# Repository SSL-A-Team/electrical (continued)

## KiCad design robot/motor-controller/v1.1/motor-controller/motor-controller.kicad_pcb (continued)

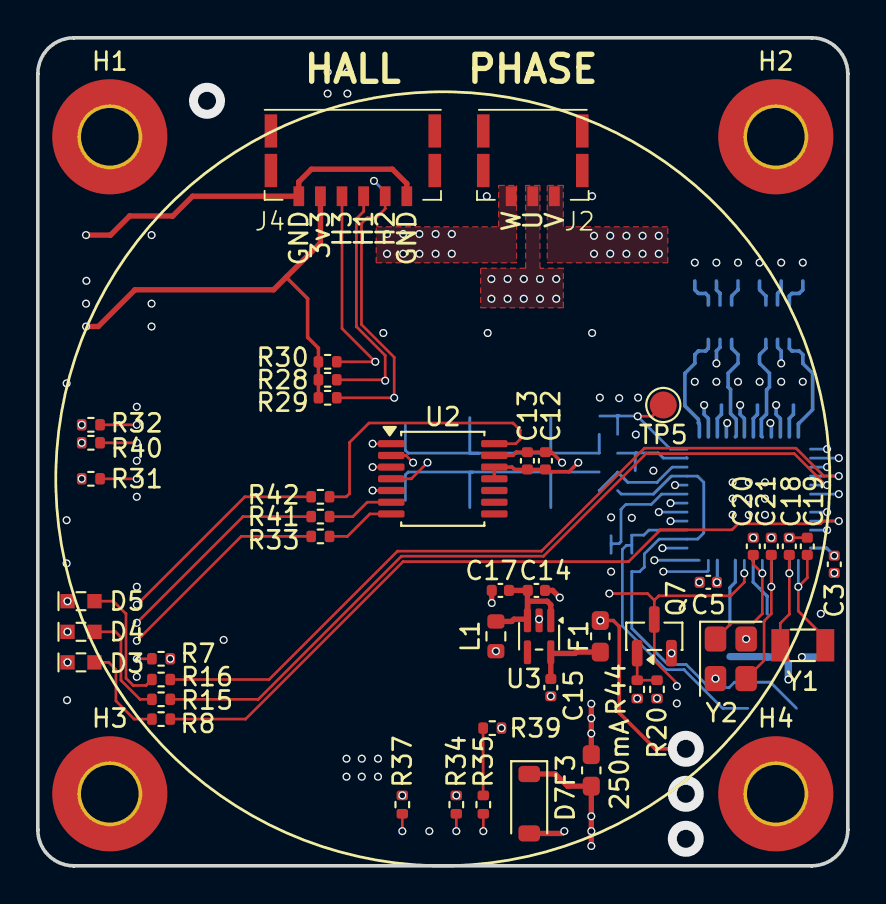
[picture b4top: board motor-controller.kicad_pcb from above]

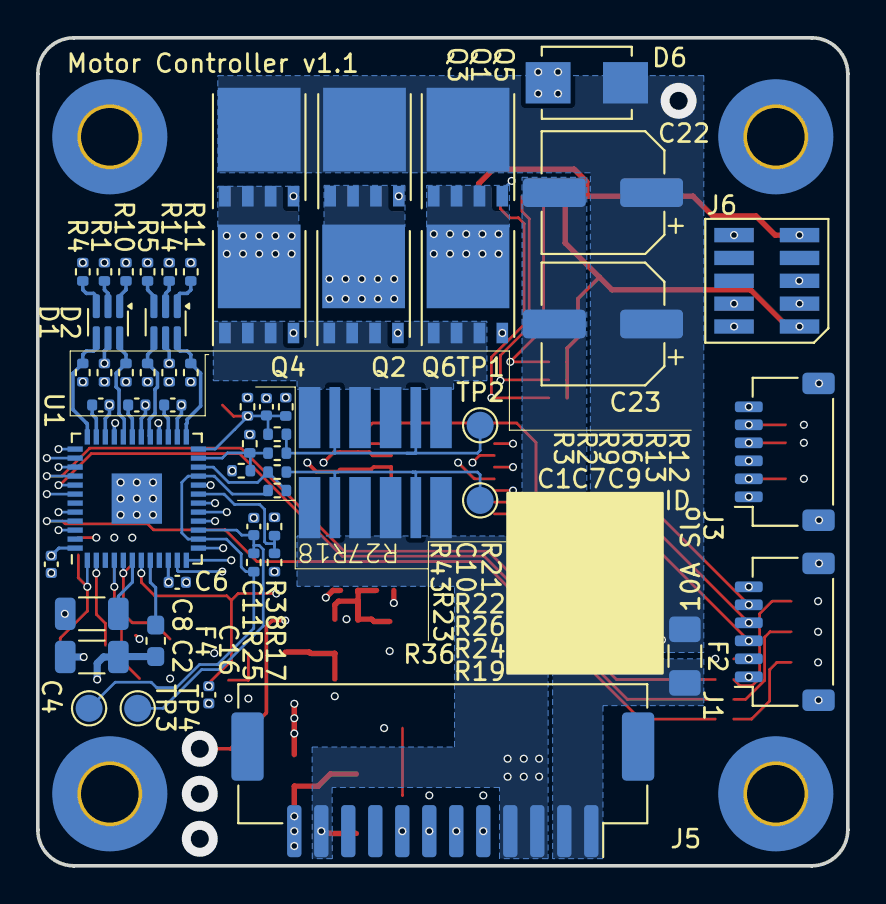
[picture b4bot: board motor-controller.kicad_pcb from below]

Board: 6 copper layers, 45.0 x 46.0 mm, 106 parts (57 on the bottom side), 76 nets.

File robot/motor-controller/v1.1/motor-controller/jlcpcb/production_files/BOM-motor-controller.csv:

Comment,Designator,Footprint,LCSC,Quantity
0,"R33,R39,R41,R42",R_0402_1005Metric,C17168,4
0.1uF 63V,"C1,C13,C14,C16,C4,C6,C7,C9",C_0402_1005Metric,C131394,8
0467.250NRHF,F3,Fuse_0603_1608Metric_Pad1.05x0.95mm_HandSolder,C151137,1
0501010.WR1,F2,Fuse_1206_3216Metric_Pad1.42x1.75mm_HandSolder,C207003,1
06F-0200L1,"F1,F4",Fuse_0603_1608Metric_Pad1.05x0.95mm_HandSolder,C377220,2
10,"R1,R10,R11,R14,R4,R5",R_0402_1005Metric,C25077,6
100k,"R20,R34,R37",R_0402_1005Metric,C25741,3
10k,"R15,R16,R28,R29,R30,R31,R32,R40,R44,R7,R8",R_0402_1005Metric,C60490,11
11.5k,R17,R_0402_1005Metric,C270653,1
11pF,"C20,C21",C_0402_1005Metric,C161525,2
13.7k 1%,R19,R_0402_1005Metric,C852522,1
15.0k 1%,R36,R_0402_1005Metric,C853539,1
15pF,"C18,C19",C_0402_1005Metric,C86285,2
165k 1%,R23,R_0402_1005Metric,C1509613,1
1k,R38,R_0402_1005Metric,C11702,1
1k 1%,,R_0402_1005Metric,C11702,0
1uF 10V,"C11,C12,C15,C17,C3,C5",C_0402_1005Metric,C14445,6
1uF 63V,"C2,C8",C_1206_3216Metric,C70463,2
2.49k 1%,"R22,R24,R26",R_0402_1005Metric,C852700,3
22uF 6.3V,C10,C_0402_1005Metric,C415703,1
30k 1%,,R_0402_1005Metric,C25776,0
330,R35,R_0402_1005Metric,C25104,1
62,"R12,R13,R2,R3,R6,R9",R_0402_1005Metric,C100501,6
62 1%,R25,R_0402_1005Metric,C852875,1
650 @100MHz,L1,R_0603_1608Metric,C21189,1
AS5047P,U2,TSSOP-14_4.4x5mm_P0.65mm,C962063,1
BAS16VY,"D1,D2",SOT-363_SC-70-6,C135826,2
BM03B-ACHFKS,J2,JST_ACHFR_03V,C5177195,1
BM06B-ACHFKS,J4,JST_ACHFR_06V,C5304907,1
BSS138K,Q7,SOT-23,C5224263,1
Conn_ARM_JTAG_SWD_10,J6,Samtec-2x5pin-1.27mm,C448647,1
EEEFT1V101AP,"C22,C23",CP_Elec_6.3x5.8,C128464,2
HoLLR2512-3W-100mR-1%,"R18,R27",2512_CS_ADI-TypeC,C2994646,2
Q13FC13500005,Y1,Crystal_SMD_3215-2Pin_3.2x1.5mm,C841881,1
SM06B-SRSS-TB,J3,JST_SH_SM06B-SRSS-TB_1x06-1MP_P1.00mm_Horizontal,C160405,1
SMBJ26CA,D6,D_SMB_Non-Polar,C135063,1
SMF3.3CA,D7,D_SOD-123,C6165153,1
STL90N10F7,"Q1,Q2,Q3,Q4,Q5,Q6",PowerFLAT_5x6,C457493,6
STSPIN32F0B,U1,QFN-48-1EP_7x7mm_P0.5mm_EP2.8x2.8mm,C1521053,1
TAXM8M4RDBCCT2T,Y2,Crystal_SMD_3225-4Pin_3.2x2.5mm,C400090,1
TLV70030_SOT353,U3,SOT-353_SC-70-5,C527437,1
XL-1608SURC-06,D5,LED0603,C965799,1
XL-1608UGC-04,D4,LED0603,C965804,1
XL-1608UOC-06,D3,LED0603,C965800,1
SM12B-ZESS,J5,JST_ZE_SM12B-ZESS-TB_1x12-1MP_P1.50mm_Horizontal,,1

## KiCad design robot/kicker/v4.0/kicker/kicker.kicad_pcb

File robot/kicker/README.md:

# Kicker Boards

Subfolders contain various versions of the kicker board. A summary is included below.

## Kicker Version Summary

 - v1.1.0_fe - Nonviable, check errata
 - v1.1.0_ufd - Nonviable, check errata
 - v1.0.0 - Nonviable, check errata
 - v2.0.0 - Patchable, check errata
 - v3.0 - Patchable, check errata
 - v3.1 - Functional, minor patching suggested

## KiCad Version Summary

 - v3.1 - KiCad v7.X
 - v3.0 - KiCad v7.X
 - v2.0.0 - KiCad v7.X
 - v1.1.0 - KiCad v7.X
 - v1.0.0 - KiCad v6.99 (nightly)

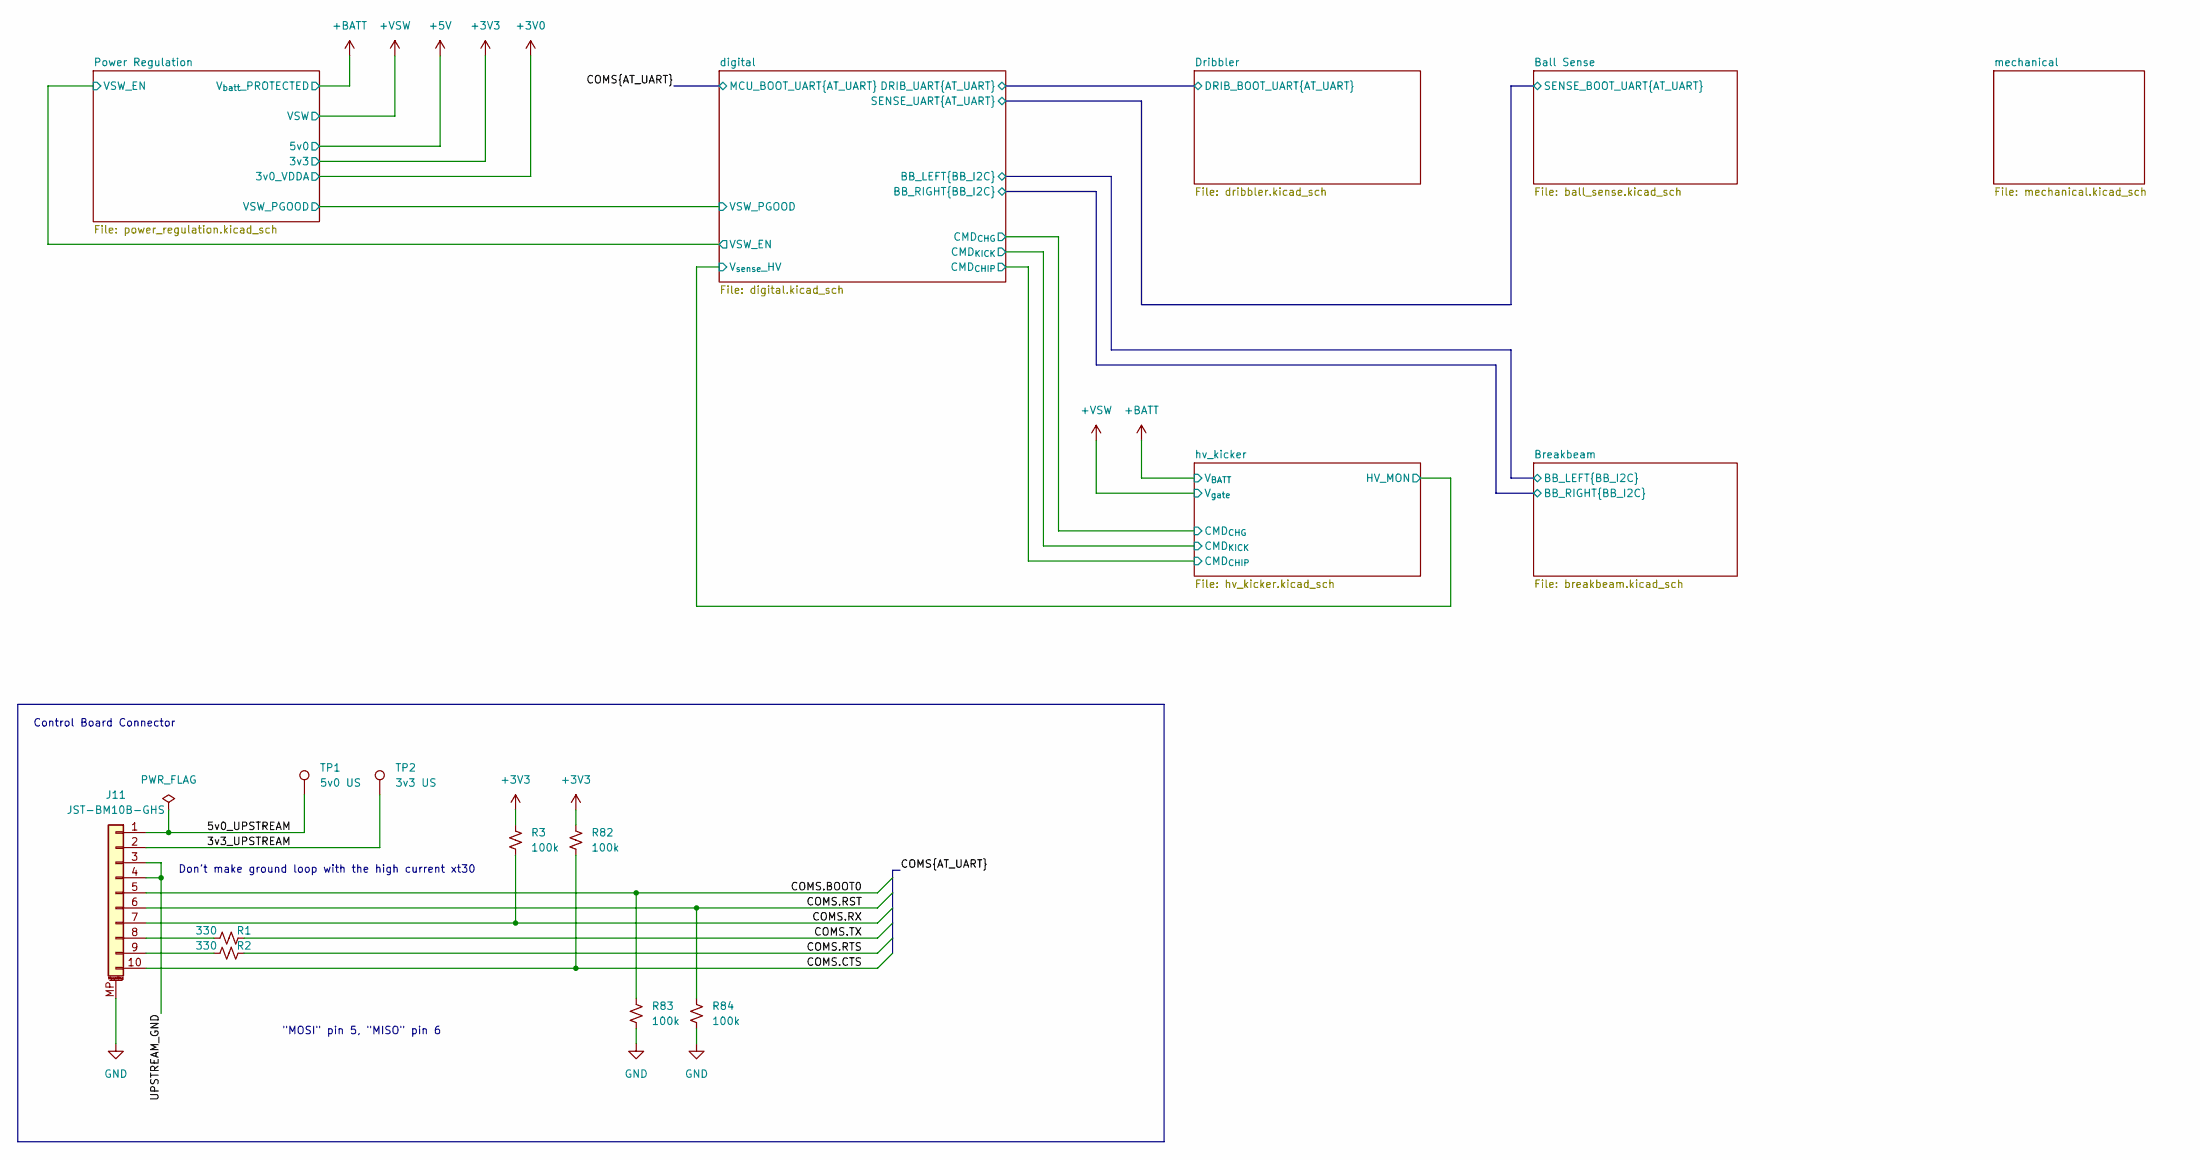
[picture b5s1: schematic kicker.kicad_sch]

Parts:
J11: JST-BM10B-GHS; JST_GH_BM10B-GHS-TBT_1x10-1MP_P1.25mm_Vertical; LCSC C2683602
R1, R2: 330; R_0402_1005Metric; LCSC C105875
R3, R82, R83, R84: 100k; R_0402_1005Metric; LCSC C60491
TP1: 5v0 US; TestPoint_Pad_D1.0mm
TP2: 3v3 US; TestPoint_Pad_D1.0mm

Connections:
+3V3: R3.1, R82.1; also elsewhere on the board
/3v3_UPSTREAM: J11.2, TP2.1
/5v0_UPSTREAM: J11.1, TP1.1
/COMS.BOOT0: J11.5, R83.1; also elsewhere on the board
/COMS.CTS: J11.10, R82.2; also elsewhere on the board
/COMS.RST: J11.6, R84.1; also elsewhere on the board
/COMS.RTS: R2.2; also elsewhere on the board
/COMS.RX: J11.7, R3.2; also elsewhere on the board
/COMS.TX: R1.2; also elsewhere on the board
/UPSTREAM_GND: J11.3, J11.4
GND: J11.MP (MountPin), R83.2, R84.2; also elsewhere on the board
unnamed: J11.8, R1.1
unnamed: J11.9, R2.1

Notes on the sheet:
Don't make ground loop with the high current xt30
Control Board Connector
"MOSI" pin 5, "MISO" pin 6

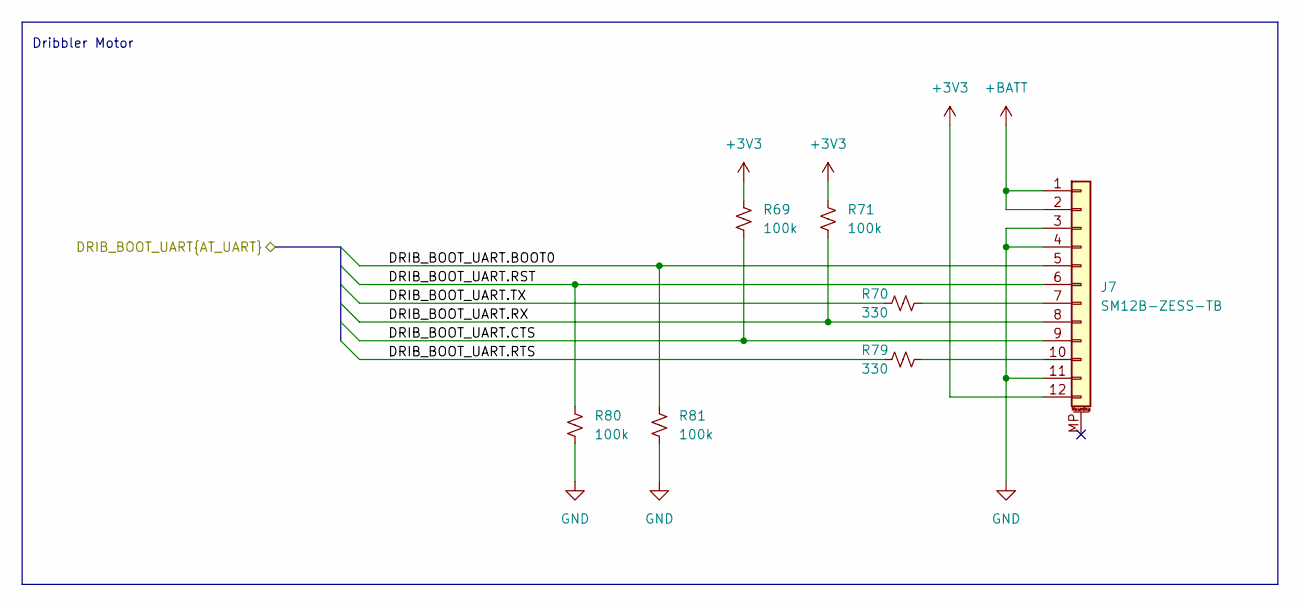
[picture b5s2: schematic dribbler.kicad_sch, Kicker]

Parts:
J7: SM12B-ZESS-TB; JST_ZE_BM12B-ZESS-TBT_1x12-1MP_P1.50mm_Vertical
R69, R71, R80, R81: 100k; R_0402_1005Metric; LCSC C60491
R70, R79: 330; R_0402_1005Metric; LCSC C105875

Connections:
+3V3: J7.12, R69.1, R71.1; also elsewhere on the board
+BATT: J7.1, J7.2; also elsewhere on the board
/Dribbler/DRIB_BOOT_UART.BOOT0: J7.5, R81.1; also elsewhere on the board
/Dribbler/DRIB_BOOT_UART.CTS: J7.9, R69.2; also elsewhere on the board
/Dribbler/DRIB_BOOT_UART.RST: J7.6, R80.1; also elsewhere on the board
/Dribbler/DRIB_BOOT_UART.RTS: R79.1; also elsewhere on the board
/Dribbler/DRIB_BOOT_UART.RX: J7.8, R71.2; also elsewhere on the board
/Dribbler/DRIB_BOOT_UART.TX: R70.1; also elsewhere on the board
GND: J7.3, J7.4, J7.11, R80.2, R81.2; also elsewhere on the board
unnamed: J7.7, R70.2
unnamed: J7.10, R79.2

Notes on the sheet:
Dribbler Motor

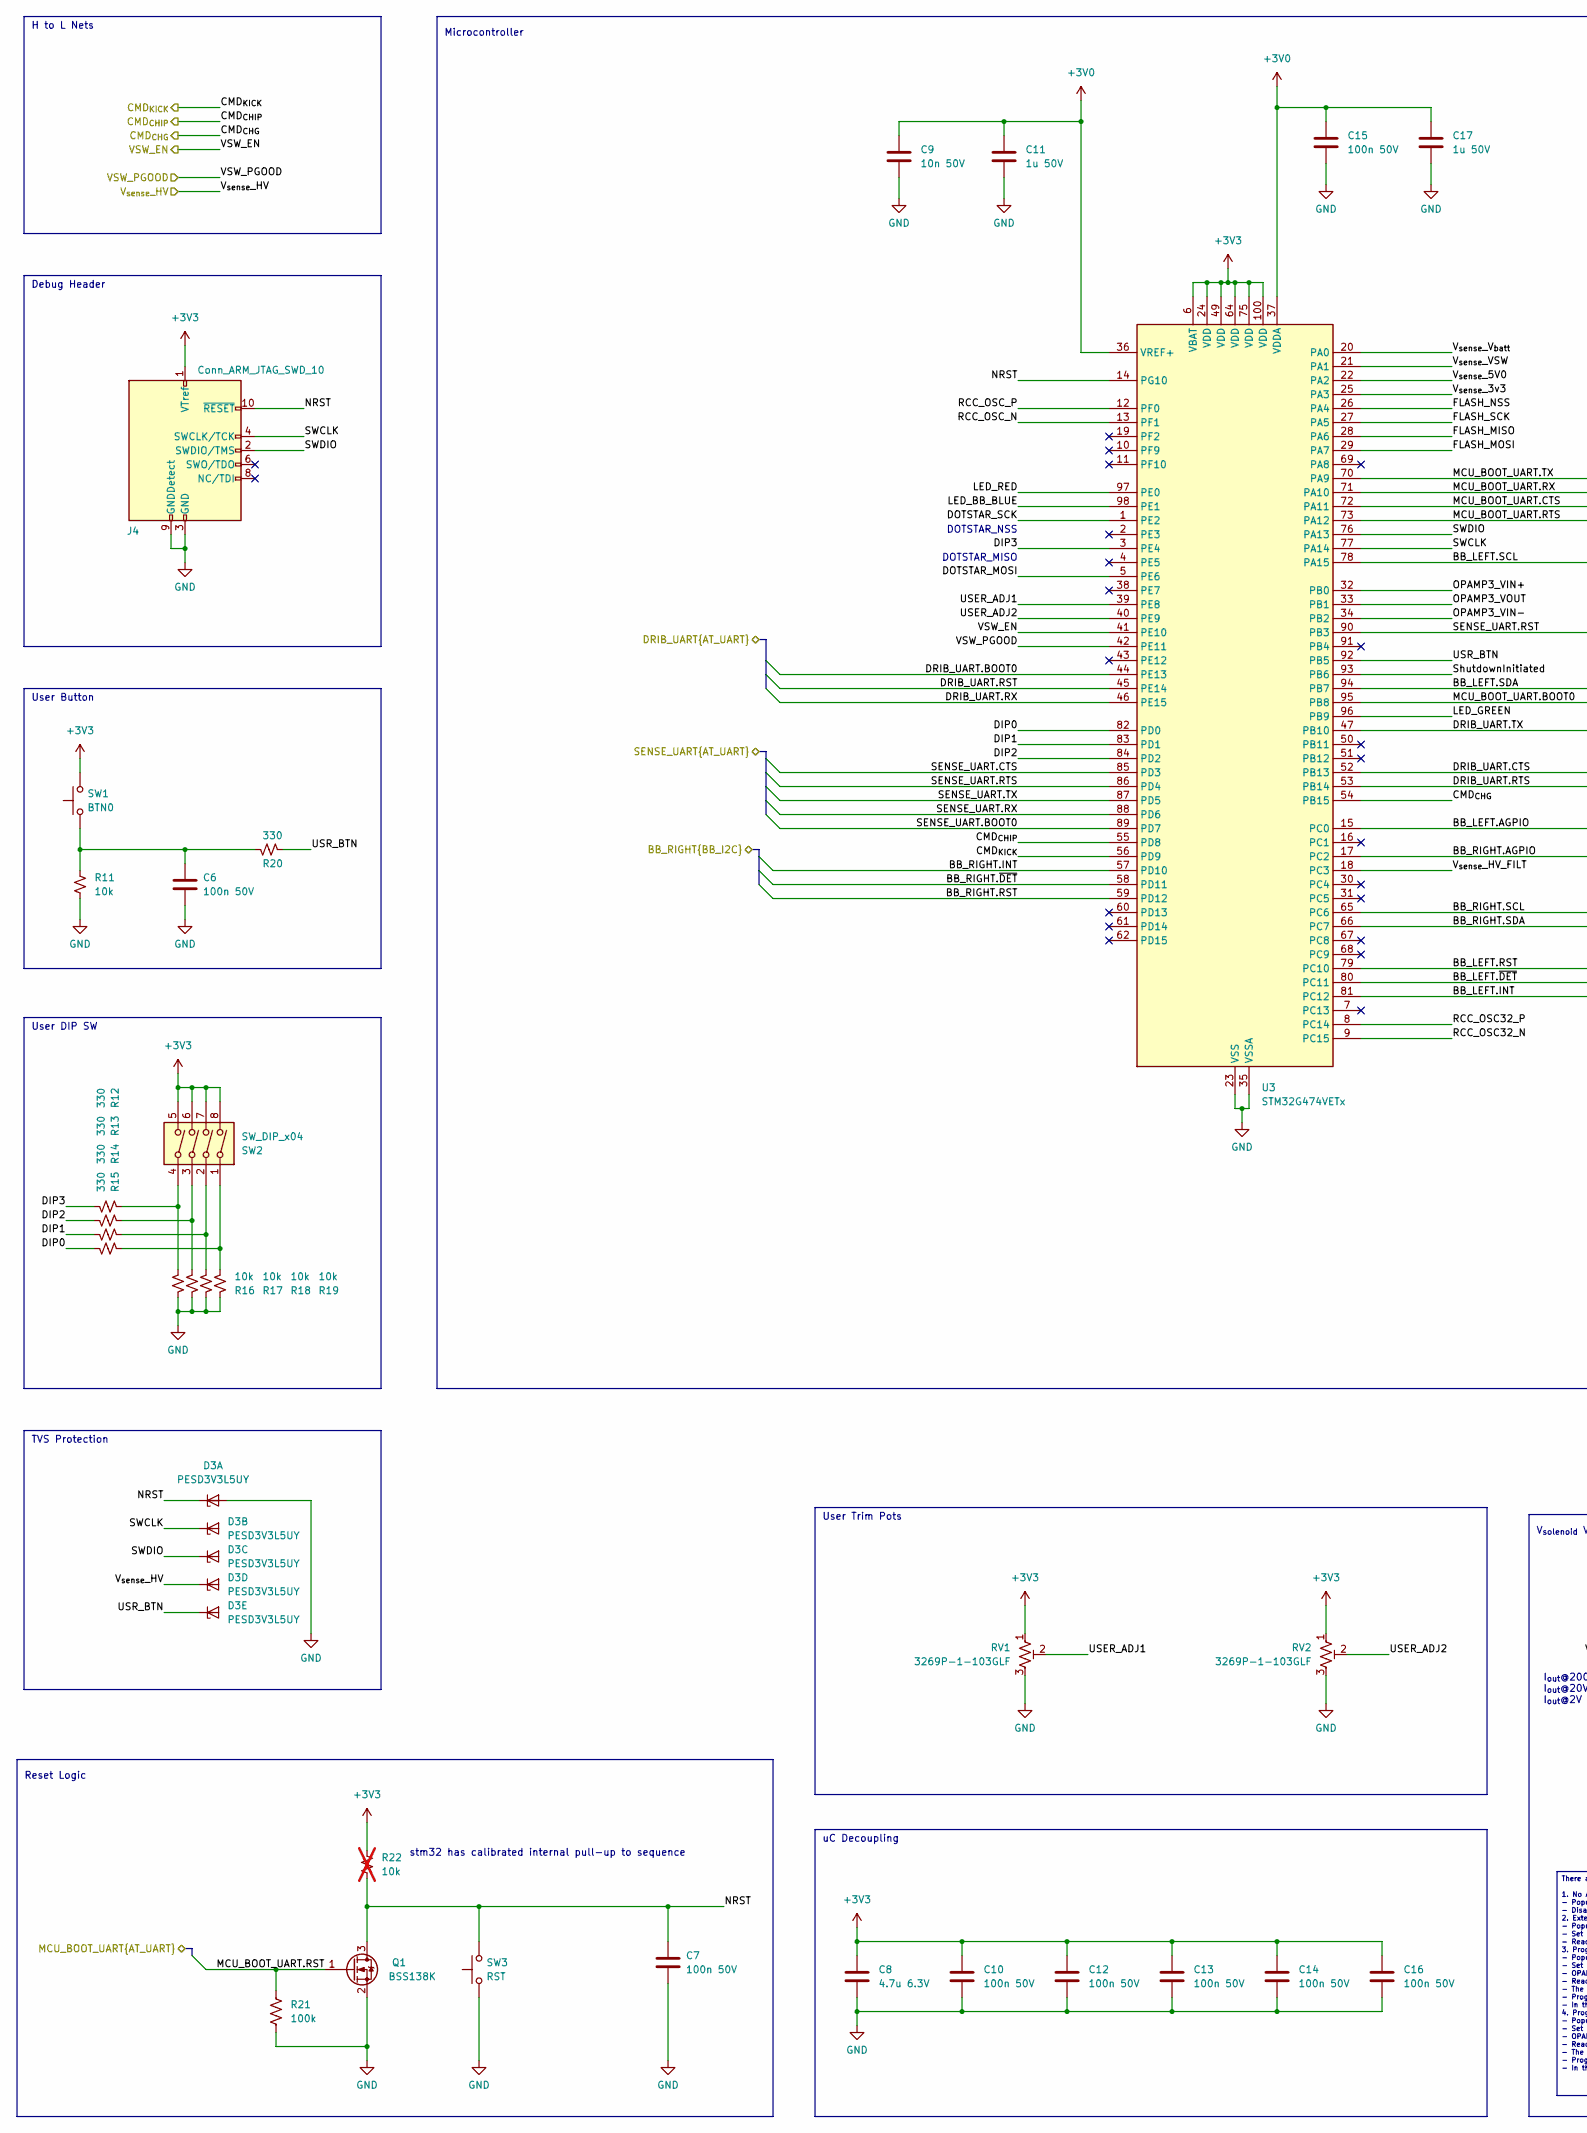
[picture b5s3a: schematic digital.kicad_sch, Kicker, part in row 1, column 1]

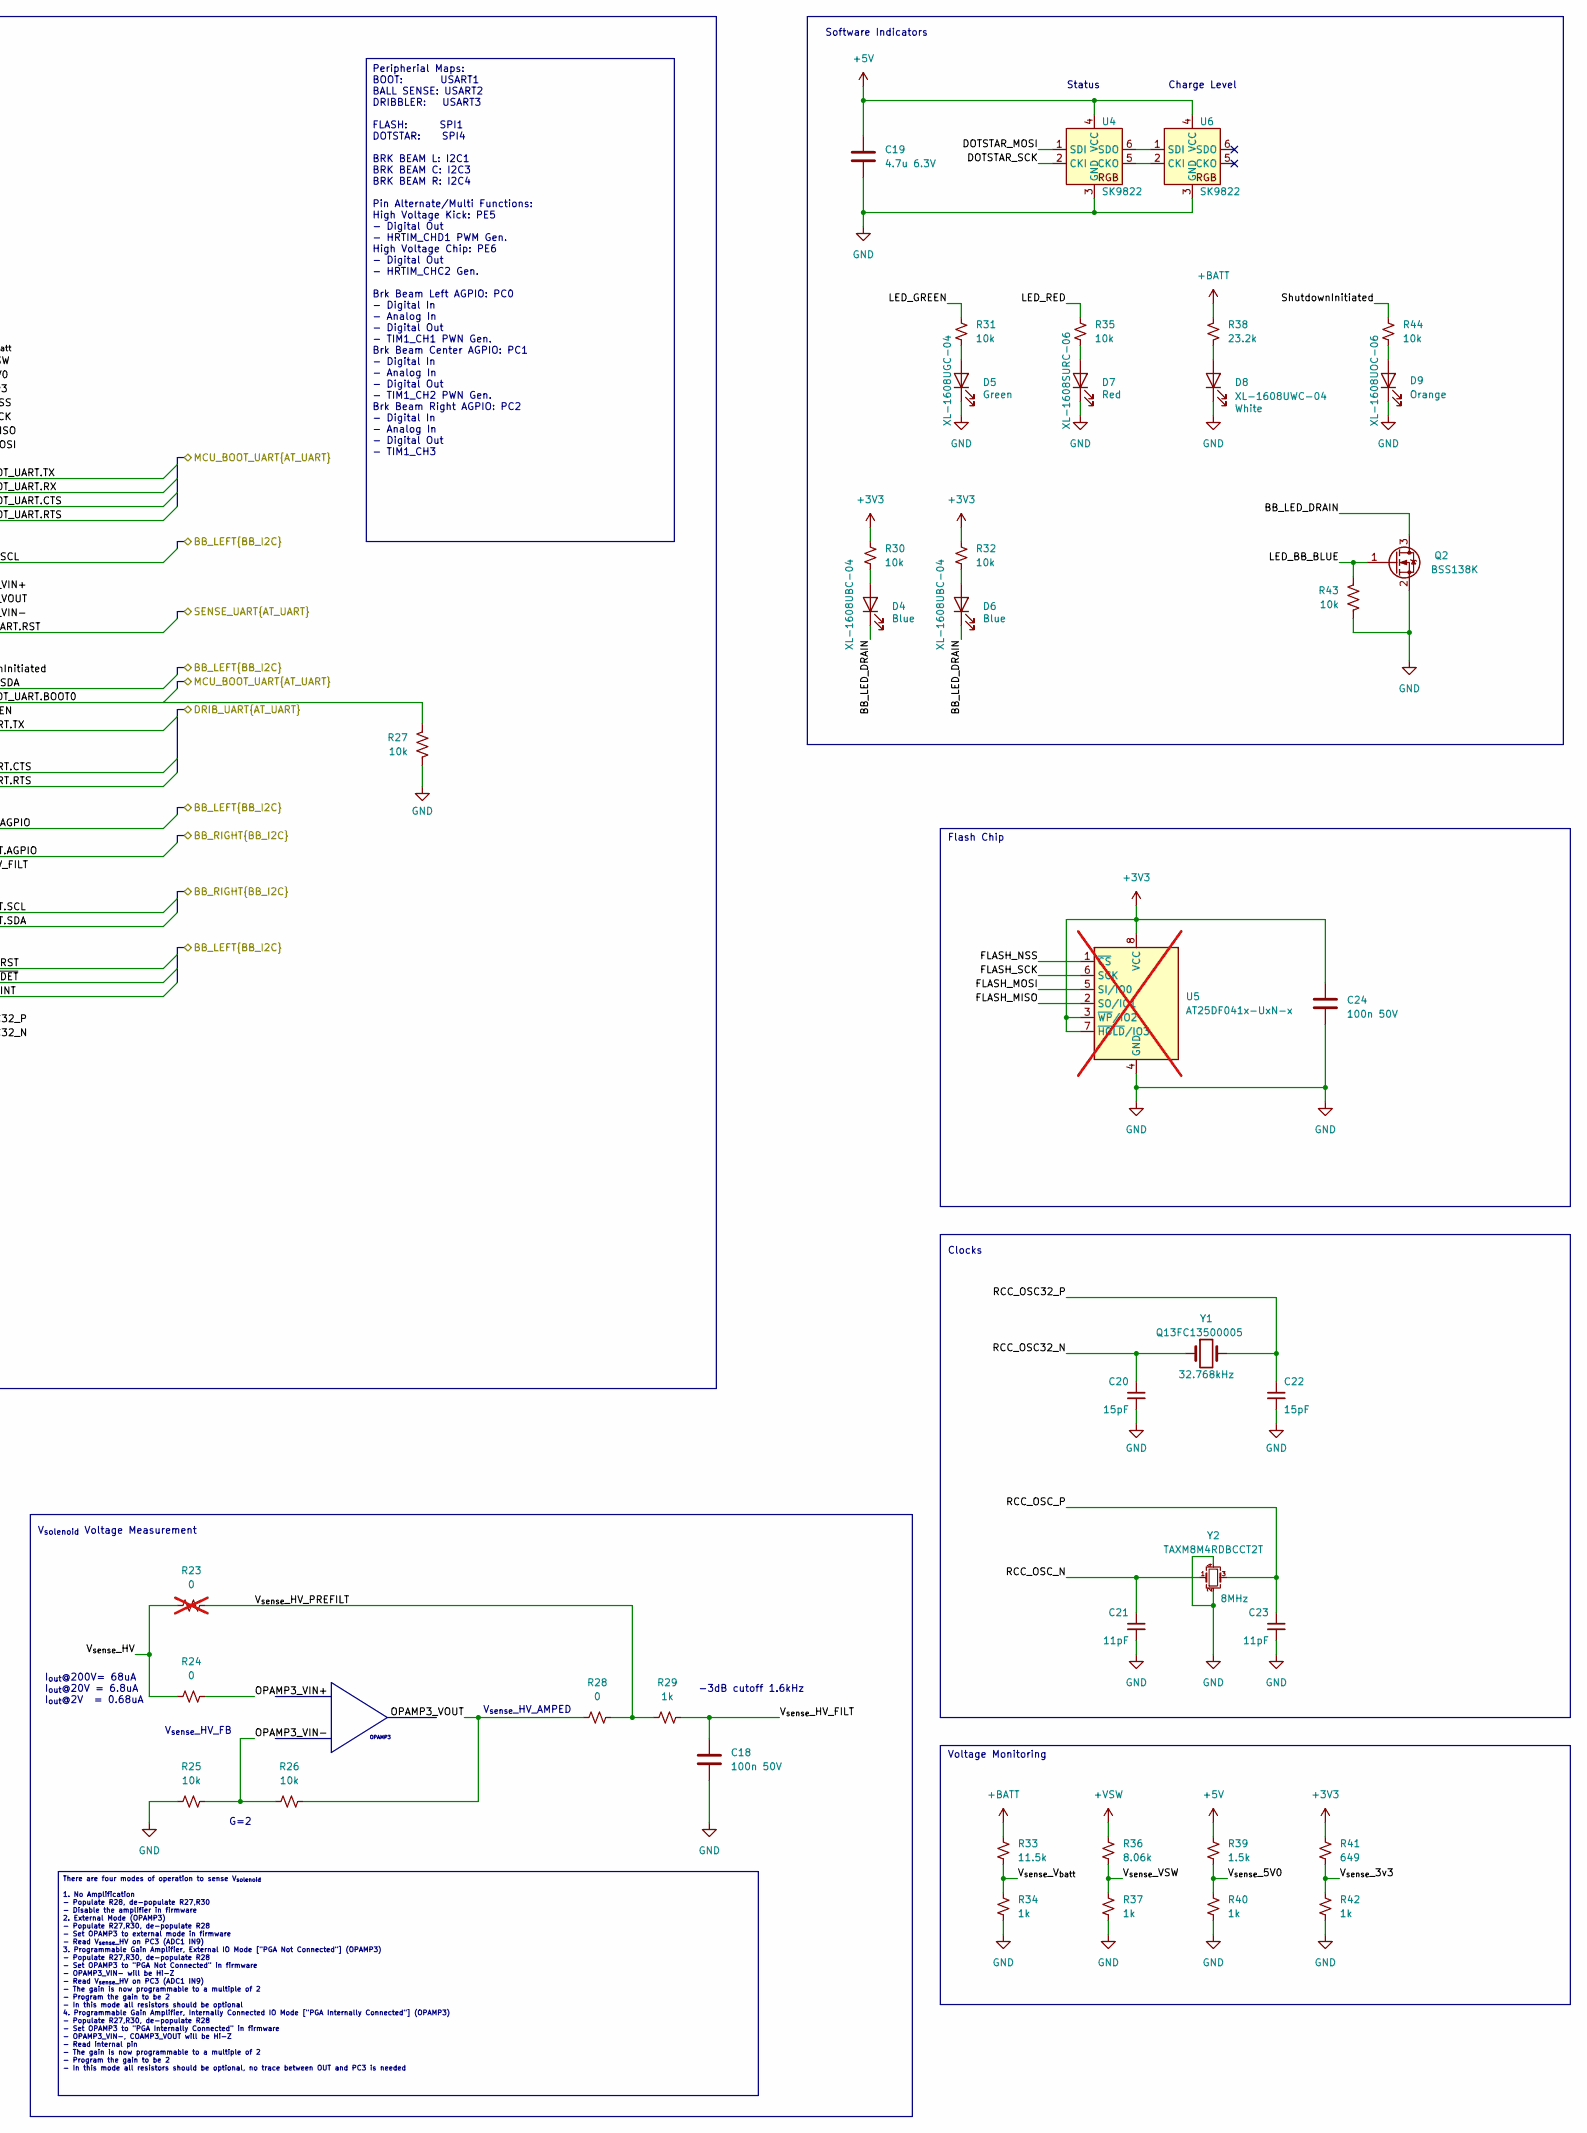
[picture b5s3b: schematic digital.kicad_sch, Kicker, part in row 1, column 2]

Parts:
C6, C7, C10, C12, C13, C14, C15, C16, C18, C24: 100n 50V; C_0402_1005Metric; LCSC C307331
C8, C19: 4.7u 6.3V; C_0402_1005Metric; LCSC C76995
C9: 10n 50V; C_0402_1005Metric; LCSC C77019
C11, C17: 1u 50V; C_0402_1005Metric; LCSC C1518208
C20, C22: 15pF; C_0402_1005Metric; LCSC C88877
C21, C23: 11pF; C_0402_1005Metric; LCSC C161525
D3: PESD3V3L5UY; SOT-363_SC-70-6; LCSC C477992
D4, D6: XL-1608UBC-04; LED0603; LCSC C965807
D5: XL-1608UGC-04; LED0603; LCSC C965804
D7: XL-1608SURC-06; LED0603; LCSC C965799
D8: XL-1608UWC-04; LED0603; LCSC C965808
D9: XL-1608UOC-06; LED0603; LCSC C965800
J4: Conn_ARM_JTAG_SWD_10; Samtec-2x5pin-1.27mm; LCSC C448647
Q1, Q2: BSS138K; SOT-23; LCSC C255592
R11, R16, R17, R18, R19, R25, R26, R27, R30, R31, R32, R35, R43, R44: 10k; R_0402_1005Metric; LCSC C60490
R12, R13, R14, R15, R20: 330; R_0402_1005Metric; LCSC C105875
R21: 100k; R_0402_1005Metric; LCSC C60491
R22: 10k; R_0402_1005Metric; LCSC C60490; not fitted
R23: 0; R_0402_1005Metric; LCSC C106231; not fitted
R24, R28: 0; R_0402_1005Metric; LCSC C106231
R29, R34, R37, R40, R42: 1k; R_0402_1005Metric; LCSC C11702
R33: 11.5k; R_0402_1005Metric; LCSC C270653
R36: 8.06k; R_0402_1005Metric; LCSC C276278
R38: 23.2k; R_0402_1005Metric; LCSC C163477
R39: 1.5k; R_0402_1005Metric; LCSC C25867
R41: 649; R_0402_1005Metric; LCSC C82294
RV1, RV2: 3269P-1-103GLF; Potentiometer_Bourns_3269P_Horizontal
SW1: BTN0; SW_SPST_TL3305A; LCSC C2886902
SW2: SW_DIP_x04; CHP-041TB
SW3: RST; SW_SPST_TL3305A; LCSC C2886902
U3: STM32G474VETx; LQFP-100_14x14mm_P0.5mm; LCSC C431632
U4, U6: SK9822; LCSC C2829089
U5: AT25DF041x-UxN-x; SOIC-8_3.9x4.9mm_P1.27mm; not fitted
Y1: Q13FC13500005; Crystal_SMD_3215-2Pin_3.2x1.5mm; LCSC C841881
Y2: TAXM8M4RDBCCT2T; Crystal_SMD_3225-4Pin_3.2x2.5mm; LCSC C400090

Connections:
+3V0: C9.1, C11.1, C15.1, C17.1, U3.36 (VREF+), U3.37 (VDDA); also elsewhere on the board
+3V3: C8.2, C10.1, C12.1, C13.1, C14.1, C16.1, C24.2, J4.1 (VTref), R22.1, R30.1, R32.1, R41.1, RV1.1, RV2.1, SW1.2, SW2.5, SW2.6, SW2.7, SW2.8, U3.6 (VBAT), U3.24 (VDD), U3.49 (VDD), U3.64 (VDD), U3.75 (VDD), U3.100 (VDD), U5.3 (~WP/IO2), U5.7 (~HOLD/IO3), U5.8 (VCC); also elsewhere on the board
+5V: C19.2, R39.1, U4.4 (VCC), U6.4 (VCC); also elsewhere on the board
+BATT: R33.1, R38.1; also elsewhere on the board
+VSW: R36.1; also elsewhere on the board
/Ball Sense/SENSE_BOOT_UART.BOOT0: U3.89 (PD7); also elsewhere on the board
/Ball Sense/SENSE_BOOT_UART.CTS: U3.85 (PD3); also elsewhere on the board
/Ball Sense/SENSE_BOOT_UART.RST: U3.90 (PB3); also elsewhere on the board
/Ball Sense/SENSE_BOOT_UART.RTS: U3.86 (PD4); also elsewhere on the board
/Ball Sense/SENSE_BOOT_UART.RX: U3.88 (PD6); also elsewhere on the board
/Ball Sense/SENSE_BOOT_UART.TX: U3.87 (PD5); also elsewhere on the board
/Breakbeam/BB_LEFT.AGPIO: U3.15 (PC0); also elsewhere on the board
/Breakbeam/BB_LEFT.INT: U3.81 (PC12); also elsewhere on the board
/Breakbeam/BB_LEFT.RST: U3.79 (PC10); also elsewhere on the board
/Breakbeam/BB_LEFT.SCL: U3.78 (PA15); also elsewhere on the board
/Breakbeam/BB_LEFT.SDA: U3.94 (PB7); also elsewhere on the board
/Breakbeam/BB_LEFT.~DET: U3.80 (PC11); also elsewhere on the board
/Breakbeam/BB_RIGHT.AGPIO: U3.17 (PC2); also elsewhere on the board
/Breakbeam/BB_RIGHT.INT: U3.57 (PD10); also elsewhere on the board
/Breakbeam/BB_RIGHT.RST: U3.59 (PD12); also elsewhere on the board
/Breakbeam/BB_RIGHT.SCL: U3.65 (PC6); also elsewhere on the board
/Breakbeam/BB_RIGHT.SDA: U3.66 (PC7); also elsewhere on the board
/Breakbeam/BB_RIGHT.~DET: U3.58 (PD11); also elsewhere on the board
/COMS.BOOT0: R27.2, U3.95 (PB8); also elsewhere on the board
/COMS.CTS: U3.72 (PA11); also elsewhere on the board
/COMS.RST: Q1.1 (G), R21.1; also elsewhere on the board
/COMS.RTS: U3.73 (PA12); also elsewhere on the board
/COMS.RX: U3.71 (PA10); also elsewhere on the board
/COMS.TX: U3.70 (PA9); also elsewhere on the board
/Dribbler/DRIB_BOOT_UART.BOOT0: U3.44 (PE13); also elsewhere on the board
/Dribbler/DRIB_BOOT_UART.CTS: U3.52 (PB13); also elsewhere on the board
/Dribbler/DRIB_BOOT_UART.RST: U3.45 (PE14); also elsewhere on the board
/Dribbler/DRIB_BOOT_UART.RTS: U3.53 (PB14); also elsewhere on the board
/Dribbler/DRIB_BOOT_UART.RX: U3.46 (PE15); also elsewhere on the board
/Dribbler/DRIB_BOOT_UART.TX: U3.47 (PB10); also elsewhere on the board
/Power Regulation/VSW_PGOOD: U3.42 (PE11); also elsewhere on the board
/digital/BB_LED_DRAIN: D4.1 (K), D6.1 (K), Q2.3 (D)
/digital/CMD_{CHG}: U3.54 (PB15); also elsewhere on the board
/digital/CMD_{CHIP}: U3.55 (PD8); also elsewhere on the board
/digital/CMD_{KICK}: U3.56 (PD9); also elsewhere on the board
/digital/DIP0: R15.2, U3.82 (PD0)
/digital/DIP1: R14.2, U3.83 (PD1)
/digital/DIP2: R13.2, U3.84 (PD2)
/digital/DIP3: R12.2, U3.3 (PE4)
/digital/DOTSTAR_MOSI: U3.5 (PE6), U4.1 (SDI)
/digital/DOTSTAR_SCK: U3.1 (PE2), U4.2 (CKI)
/digital/FLASH_MISO: U3.28 (PA6), U5.2 (SO/IO1)
/digital/FLASH_MOSI: U3.29 (PA7), U5.5 (SI/IO0)
/digital/FLASH_NSS: U3.26 (PA4), U5.1 (~CS)
/digital/FLASH_SCK: U3.27 (PA5), U5.6 (SCK)
/digital/LED_BB_BLUE: Q2.1 (G), R43.2, U3.98 (PE1)
/digital/LED_GREEN: R31.1, U3.96 (PB9)
/digital/LED_RED: R35.1, U3.97 (PE0)
/digital/NRST: C7.1, D3.1 (K1), J4.10 (~RESET), Q1.3 (D), R22.2, SW3.2, U3.14 (PG10)
/digital/OPAMP3_VIN+: R24.2, U3.32 (PB0)
/digital/OPAMP3_VIN-: R25.1, R26.1, U3.34 (PB2)
/digital/OPAMP3_VOUT: R26.2, R28.1, U3.33 (PB1)
/digital/RCC_OSC32_N: C20.1, U3.9 (PC15), Y1.1
/digital/RCC_OSC32_P: C22.1, U3.8 (PC14), Y1.2
/digital/RCC_OSC_N: C21.1, U3.13 (PF1), Y2.1
/digital/RCC_OSC_P: C23.1, U3.12 (PF0), Y2.3
/digital/SWCLK: D3.3 (K2), J4.4 (SWCLK/TCK), U3.77 (PA14)
/digital/SWDIO: D3.4 (K3), J4.2 (SWDIO/TMS), U3.76 (PA13)
/digital/ShutdownInitiated: R44.1, U3.93 (PB6)
/digital/USER_ADJ1: RV1.2, U3.39 (PE8)
/digital/USER_ADJ2: RV2.2, U3.40 (PE9)
/digital/USR_BTN: D3.6 (K5), R20.1, U3.92 (PB5)
/digital/VSW_EN: U3.41 (PE10); also elsewhere on the board
/digital/V_{sense}_3v3: R41.2, R42.1, U3.25 (PA3)
/digital/V_{sense}_5V0: R39.2, R40.1, U3.22 (PA2)
/digital/V_{sense}_HV: D3.5 (K4), R23.1, R24.1; also elsewhere on the board
/digital/V_{sense}_HV_FILT: C18.1, R29.2, U3.18 (PC3)
/digital/V_{sense}_HV_PREFILT: R23.2, R28.2, R29.1
/digital/V_{sense}_VSW: R36.2, R37.1, U3.21 (PA1)
/digital/V_{sense}_V_{batt}: R33.2, R34.1, U3.20 (PA0)
GND: C6.2, C7.2, C8.1, C9.2, C10.2, C11.2, C12.2, C13.2, C14.2, C15.2, C16.2, C17.2, C18.2, C19.1, C20.2, C21.2, C22.2, C23.2, C24.1, D3.2 (A), D5.1 (K), D7.1 (K), D8.1 (K), D9.1 (K), J4.3 (GND), J4.5 (GND), J4.9 (GNDDetect), Q1.2 (S), Q2.2 (S), R11.2, R16.1, R17.1, R18.1, R19.1, R21.2, R25.2, R27.1, R34.2, R37.2, R40.2, R42.2, R43.1, RV1.3, RV2.3, SW3.1, U3.23 (VSS), U3.35 (VSSA), U3.48 (VSS), U3.63 (VSS), U3.74 (VSS), U3.99 (VSS), U4.3 (GND), U5.4 (GND), U6.3 (GND), Y2.2, Y2.4; also elsewhere on the board
unnamed: C6.1, R11.1, R20.2, SW1.1
unnamed: D4.2 (A), R30.2
unnamed: D5.2 (A), R31.2
unnamed: D6.2 (A), R32.2
unnamed: D7.2 (A), R35.2
unnamed: D8.2 (A), R38.2
unnamed: D9.2 (A), R44.2
unnamed: R12.1, R16.2, SW2.4
unnamed: R13.1, R17.2, SW2.3
unnamed: R14.1, R18.2, SW2.2
unnamed: R15.1, R19.2, SW2.1
unnamed: U4.5 (CKO), U6.2 (CKI)
unnamed: U4.6 (SDO), U6.1 (SDI)

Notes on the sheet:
Peripherial Maps: BOOT: USART1 BALL SENSE: USART2 DRIBBLER: USART3 FLASH: SPI1 DOTSTAR: SPI4 BRK BEAM L: I2C1 BRK BEAM C: I2C3 BRK BEAM R: I2C4 Pin Alternate/Multi Functions: High Voltage Kick: PE5 - Digital Out - HRTIM_CHD1 PWM Gen. High Voltage Chip: PE6 - Digital Out - HRTIM_CHC2 Gen. Brk Beam L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
There are four modes of operation to sense V_{solenoid} 1. No Amplification - Populate R28, de-populate R27,R30 - Disable the amplifier in firmware 2. External Mode (OPAMP3) - Populate R27,R30, de-populate R28 - Set OPAMP3 to external mode in firmware - Read V_{sense}_HV on PC3 (ADC1 IN9) 3. Progra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
User DIP SW
Microcontroller
User Trim Pots
Clocks
-3dB cutoff 1.6kHz
Flash Chip
Debug Header
DOTSTAR_MISO
User Button
Charge Level
stm32 has calibrated internal pull-up to sequence
OPAMP3
G=2
uC Decoupling
Voltage Monitoring
V_{sense}_HV_FB
H to L Nets
I_{out}@200V= 68uA I_{out}@20V = 6.8uA I_{out}@2V = 0.68uA
V_{solenoid} Voltage Measurement
Status
TVS Protection
Reset Logic
V_{sense}_HV_AMPED
Software Indicators
DOTSTAR_NSS

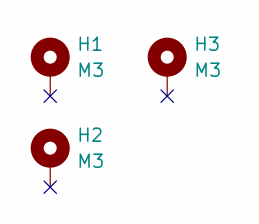
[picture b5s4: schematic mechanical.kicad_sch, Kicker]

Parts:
H1, H2, H3: M3; MountingHole_3.2mm_M3_Pad
